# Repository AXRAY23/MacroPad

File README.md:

# MacroPad
A collection of pcb and other files used in the creation of BedoDev's MacroPad.

# DISCLAIMER:
The libraries used for schematics and footprints are forked from other open source keyboard projects.
After I figure out how to use submodules i will remove them from the repo and create links to the original submodules from their respective git projects.

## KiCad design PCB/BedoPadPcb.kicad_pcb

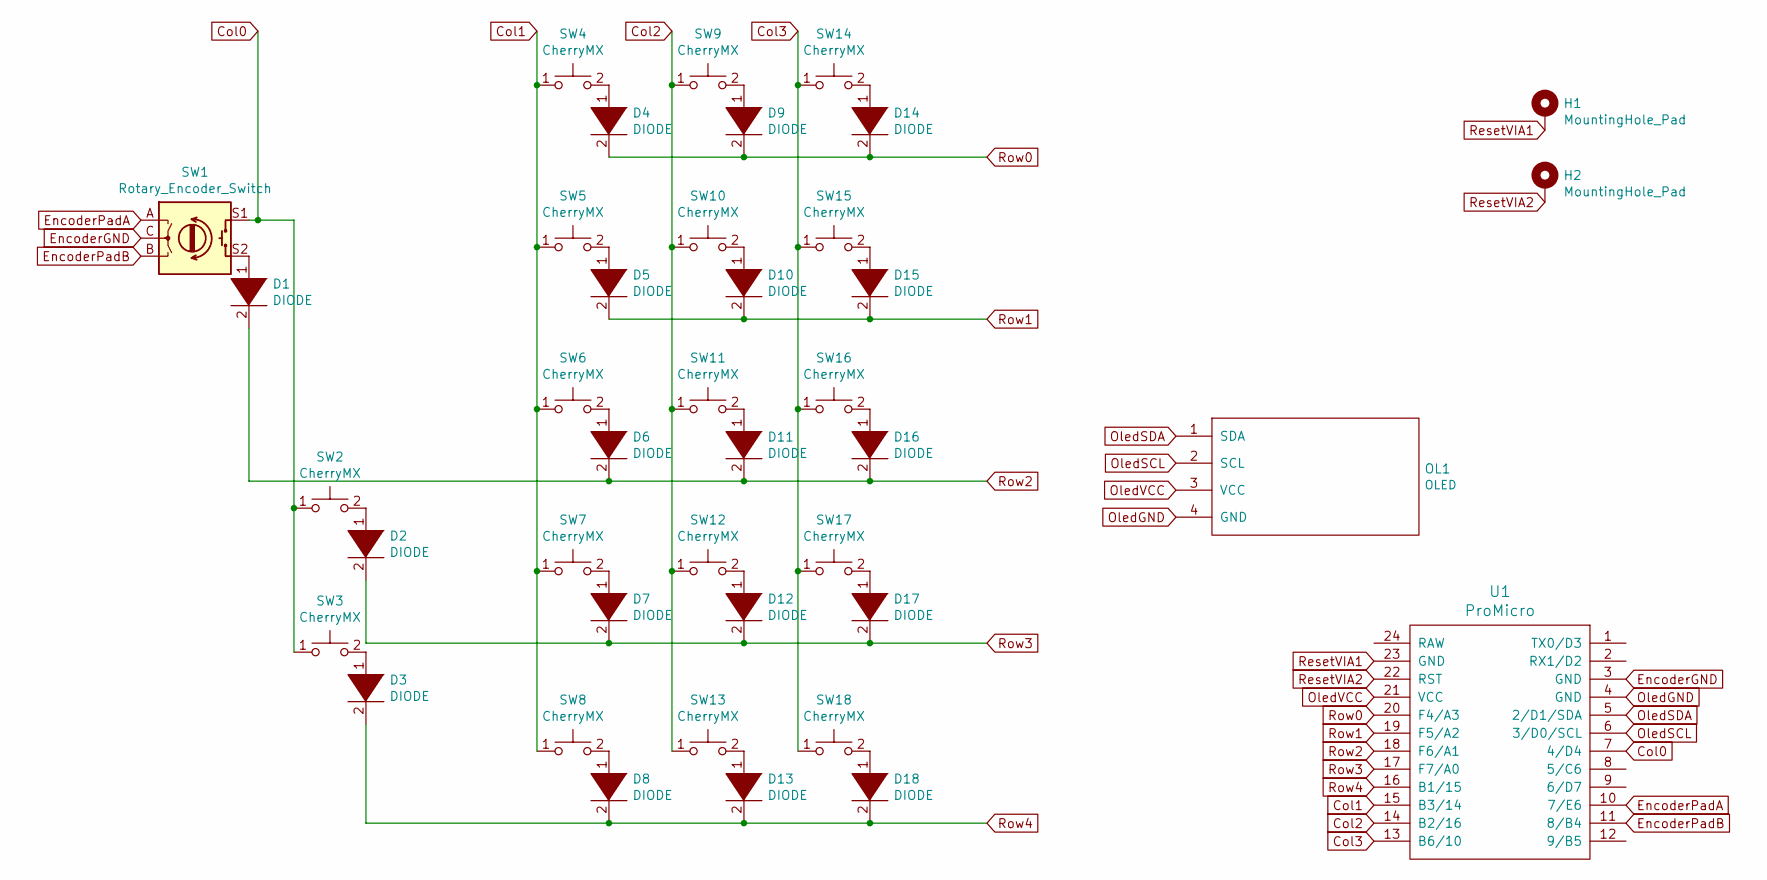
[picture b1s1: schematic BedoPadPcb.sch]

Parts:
D1, D2, D3, D4, D5, D6, D7, D8, D9, D10, D11, D12, D13, D14, D15, D16, D17, D18: DIODE; D3_TH
H1, H2: MountingHole_Pad; 1pin_conn
OL1: OLED; OLED_v2
SW1: Rotary_Encoder_Switch; RotaryEncoder_EC11
SW2, SW3, SW4, SW5, SW6, SW7, SW8, SW9, SW10, SW11, SW12, SW13, SW14, SW15, SW16, SW17, SW18: CherryMX; CherryMX_Hotswap
U1: ProMicro; ProMicro_v3

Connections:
Col0: SW1.S1, SW2.1, SW3.1, U1.7 (4/D4)
Col1: SW4.1, SW5.1, SW6.1, SW7.1, SW8.1, U1.15 (B3/14)
Col2: SW9.1, SW10.1, SW11.1, SW12.1, SW13.1, U1.14 (B2/16)
Col3: SW14.1, SW15.1, SW16.1, SW17.1, SW18.1, U1.13 (B6/10)
EncoderGND: SW1.C, U1.3 (GND)
EncoderPadA: SW1.A, U1.10 (7/E6)
EncoderPadB: SW1.B, U1.11 (8/B4)
unnamed: D1.1 (K), SW1.S2
unnamed: D2.1 (K), SW2.2
unnamed: D3.1 (K), SW3.2
unnamed: D4.1 (K), SW4.2
unnamed: D5.1 (K), SW5.2
unnamed: D6.1 (K), SW6.2
unnamed: D7.1 (K), SW7.2
unnamed: D8.1 (K), SW8.2
unnamed: D9.1 (K), SW9.2
unnamed: D10.1 (K), SW10.2
unnamed: D11.1 (K), SW11.2
unnamed: D12.1 (K), SW12.2
unnamed: D13.1 (K), SW13.2
unnamed: D14.1 (K), SW14.2
unnamed: D15.1 (K), SW15.2
unnamed: D16.1 (K), SW16.2
unnamed: D17.1 (K), SW17.2
unnamed: D18.1 (K), SW18.2
OledGND: OL1.4 (GND), U1.4 (GND)
OledSCL: OL1.2 (SCL), U1.6 (3/D0/SCL)
OledSDA: OL1.1 (SDA), U1.5 (2/D1/SDA)
OledVCC: OL1.3 (VCC), U1.21 (VCC)
ResetVIA1: H1.1, U1.23 (GND)
ResetVIA2: H2.1, U1.22 (RST)
Row0: D4.2 (A), D9.2 (A), D14.2 (A), U1.20 (F4/A3)
Row1: D5.2 (A), D10.2 (A), D15.2 (A), U1.19 (F5/A2)
Row2: D1.2 (A), D6.2 (A), D11.2 (A), D16.2 (A), U1.18 (F6/A1)
Row3: D2.2 (A), D7.2 (A), D12.2 (A), D17.2 (A), U1.17 (F7/A0)
Row4: D3.2 (A), D8.2 (A), D13.2 (A), D18.2 (A), U1.16 (B1/15)

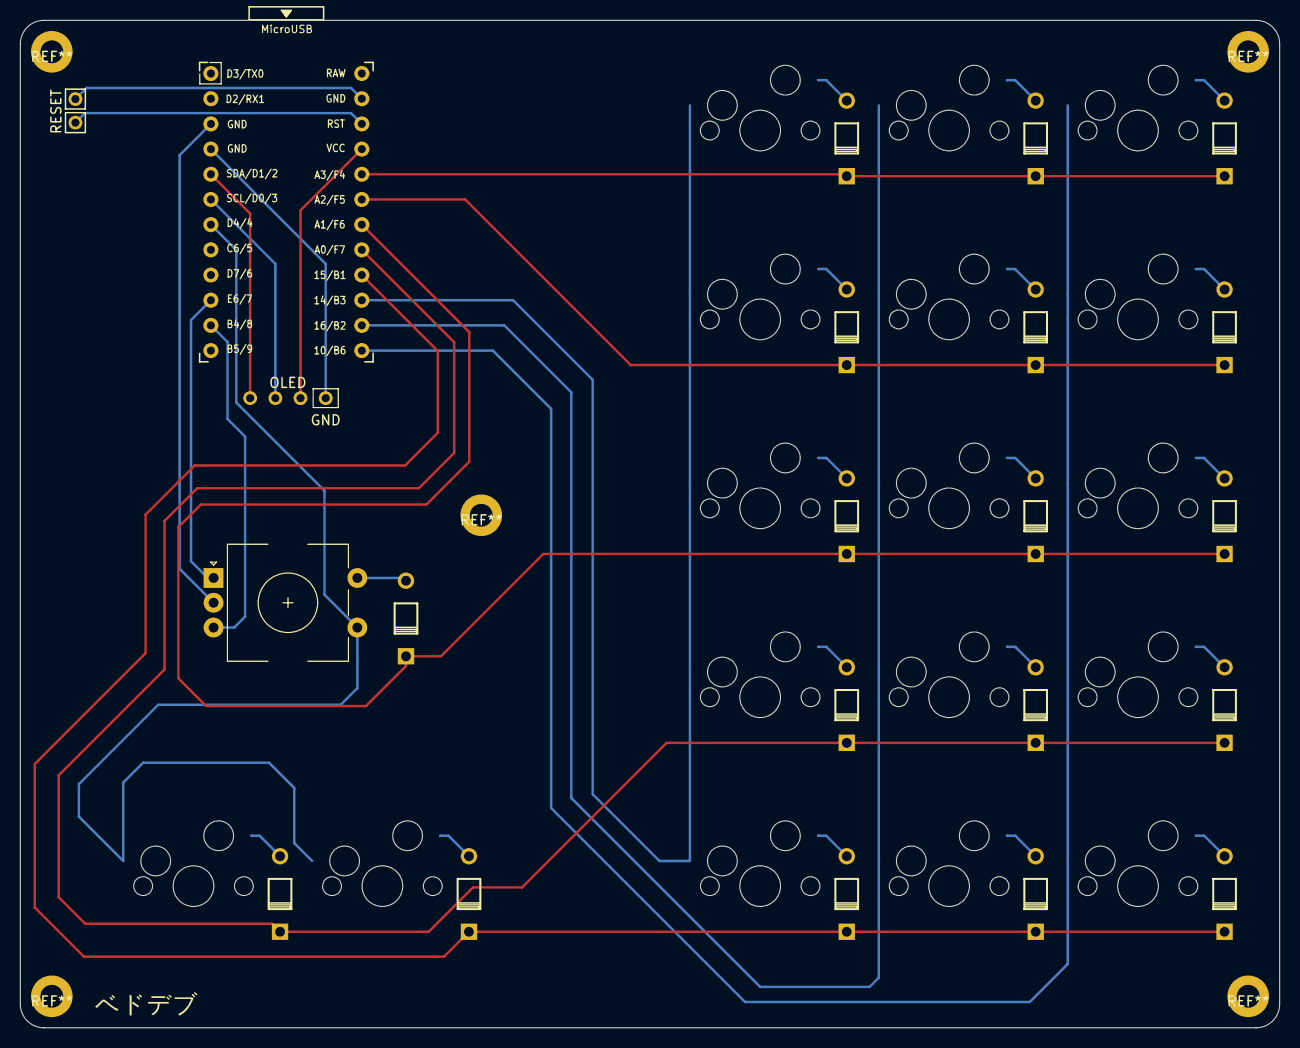
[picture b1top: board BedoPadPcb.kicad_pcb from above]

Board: 2 copper layers, 127.0 x 101.6 mm, 40 parts (0 on the bottom side), 36 nets.

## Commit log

2021-07-06 Pcb layout finished
2021-07-09 Restructure
2021-07-10 Final PCB
2021-07-13 Added a basic blank firmware
2021-07-13 Added precompiled firmware and regenerated some files
2021-07-13 Added plate svg file
2021-08-05 added finished plate
